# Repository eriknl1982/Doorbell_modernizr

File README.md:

This repository contains sample code and eagle/gerber/STL files for the Doorbell Modernizr I sell on tindie: https://www.tindie.com/products/ErikLemcke/doorbell-modernizr/

The Doorbell Modernizr is a device that can transform your ordinary doorbell (running on 8 - 24v ac) into a "smart" wifi doorbell.
Whenever someone presses your doorbell, the Doorbell Modernizr can send a signal to your home automation system (currently supported: Home assistant, Domoticz and Openhab).

If you want to program the device yourself (for example with the Arduino IDE),provide it with power, plug in a ftdi module and set the dipswitch on the pcb to on.

I use the folowing settings for programming:

- Board: Generic EP8266 module
- Flash mode: QIO
- Flash size: 512K (64K SPIFFS)
- Debugging port: Disabled
- Debug level: None
- IwIP variant: V2 lower memory
- reset method: ck
- crystal frequency: 26Mhz
- Flash frequency: 40Mhz
- CPU frequency: 80Mhz
- Builtin led: 2
- Upload speed: 115200
- Erase flash: Only sketch

If you are going to build it yourself, you will need the folowing parts:

#### To assemble this board, you will need the following parts:
- 1x ESP12f module [(sample)](https://www.aliexpress.com/item/ESP8266-Remote-Serial-WIFI-Transceiver-Wireless-Module-Esp-12-AP-STA-TOP/32646271039.html?spm=2114.search0104.3.8.2d866f9bg356HJ&ws_ab_test=searchweb0_0,searchweb201602_4_10152_10709_10151_10065_10344_10068_5722815_10342_10343_10340_5722915_10341_5722615_10696_10084_10083_10618_10304_10710_10307_10301_5722715_5711215_10059_308_100031_10103_10624_10623_10622_5711315_5722515_10621_10620,searchweb201603_36,ppcSwitch_5&algo_expid=2d4aea06-a96e-40a3-a231-87c2b62a80c4-1&algo_pvid=2d4aea06-a96e-40a3-a231-87c2b62a80c4&transAbTest=ae803_2&priceBeautifyAB=0)
- 4x 10k resitor, smd size 1206 [(sample)](https://www.aliexpress.com/item/Free-Shipping-100PCS-1206-10K-10K-OHM-1-smd-resistor/1090806202.html?spm=2114.search0104.3.1.43a21240XRFdDf&ws_ab_test=searchweb0_0,searchweb201602_4_10152_10709_10151_10065_10344_10068_5722815_10342_10343_10340_5722915_10341_5722615_10696_10084_10083_10618_10304_10710_10307_10301_5722715_5711215_10059_308_100031_10103_10624_10623_10622_5711315_5722515_10621_10620,searchweb201603_36,ppcSwitch_5&algo_expid=709525b8-8593-455c-8efa-07c3f3ce8228-0&algo_pvid=709525b8-8593-455c-8efa-07c3f3ce8228&transAbTest=ae803_2&priceBeautifyAB=0)
- 1x 10k resitor, thru hole [(sample)](https://www.aliexpress.com/store/product/100pcs-set-1-4W-Resistance-1-Metal-Film-Resistor-Pack-Assorted-Kit-1K-2K-4-7K/1504763_32861819464.html?spm=2114.search0104.3.1.4c0d36baXYxkSz&ws_ab_test=searchweb0_0,searchweb201602_4_10152_10151_10065_10344_10068_10342_10343_10340_10341_10696_10084_10083_10618_10304_10307_10820_10821_10301_10843_10059_100031_10103_10624_10623_10622_10621_10620,searchweb201603_51,ppcSwitch_5&algo_expid=e3fd0740-6222-418d-9183-fe36bdfb2f1d-0&algo_pvid=e3fd0740-6222-418d-9183-fe36bdfb2f1d&transAbTest=ae803_2&priceBeautifyAB=0)
- 1x 330r resitor, smd size 1206 [(sample)](https://www.aliexpress.com/item/100Pcs-1206-SMD-resistor-0R-10M-1-2W-0-1-10-100-150-220-330-ohm/32847115923.html?spm=2114.search0104.3.1.4bcc1954MGyEbp&ws_ab_test=searchweb0_0,searchweb201602_4_10152_10709_10151_10065_10344_10068_5722815_10342_10343_10340_5722915_10341_5722615_10696_10084_10083_10618_10304_10710_10307_10301_5722715_5711215_10059_308_100031_10103_10624_10623_10622_5711315_5722515_10621_10620,searchweb201603_36,ppcSwitch_5&algo_expid=03d36d71-9210-4daa-ba6d-0d927a84b877-0&algo_pvid=03d36d71-9210-4daa-ba6d-0d927a84b877&transAbTest=ae803_2&priceBeautifyAB=0)
- 1x 1p dip switch [(sample)](https://www.aliexpress.com/item/10PCS-Lot-DIP-Switch-1P-2-54mm-Toggle-Switch-Red-Snap-Switch/32778200806.html?spm=2114.search0104.3.24.1fe1d1a1sUUCAD&ws_ab_test=searchweb0_0,searchweb201602_4_10152_10709_10151_10065_10344_10068_5722815_10342_10343_10340_5722915_10341_5722615_10696_10084_10083_10618_10304_10710_10307_10301_5722715_5711215_10059_308_100031_10103_10624_10623_10622_5711315_5722515_10621_10620,searchweb201603_36,ppcSwitch_5&algo_expid=cc64cbff-a764-4662-8452-5fbc674b3830-3&algo_pvid=cc64cbff-a764-4662-8452-5fbc674b3830&transAbTest=ae803_2&priceBeautifyAB=0)
- 2x tactile switch [(sample)](https://www.aliexpress.com/item/THGS-25pcs-Round-Pushbutton-4-Pins-SMD-SMT-Momentary-Tactile-Switch/32721411394.html?spm=2114.search0104.3.69.24d25580z5KXIm&ws_ab_test=searchweb0_0,searchweb201602_4_10152_10709_10151_10065_10344_10068_5722815_10342_10343_10340_5722915_10341_5722615_10696_10084_10083_10618_10304_10710_10307_10301_5722715_5711215_10059_308_100031_10103_10624_10623_10622_5711315_5722515_10621_10620,searchweb201603_36,ppcSwitch_5&algo_expid=72ad9c0a-894e-4d0d-a650-c844d18cb295-12&algo_pvid=72ad9c0a-894e-4d0d-a650-c844d18cb295&transAbTest=ae803_2&priceBeautifyAB=0)
- 1x 470uf capacitor [(sample)](https://www.aliexpress.com/item/SMD-electrolytic-capacitor-470UF-6-3V-6-3-7-7MM-VT-type-chip-polarity-temperature-105/32814865187.html?spm=2114.search0104.3.87.3c9272dblaF34k&ws_ab_test=searchweb0_0,searchweb201602_4_10152_10709_10151_10065_10344_10068_5722815_10342_10343_10340_5722915_10341_5722615_10696_10084_10083_10618_10304_10710_10307_10301_5722715_5711215_10059_308_100031_10103_10624_10623_10622_5711315_5722515_10621_10620,searchweb201603_36,ppcSwitch_5&algo_expid=fa08a327-d750-4922-8d0c-8a368b171ecc-13&algo_pvid=fa08a327-d750-4922-8d0c-8a368b171ecc&transAbTest=ae803_2&priceBeautifyAB=0)
- 1x 100nf capacitor, SMD size 1206 [(sample)](https://www.aliexpress.com/item/Free-Shipping-100PCS-1206-104-100NF-0-1UF-1206-SMD-capacitance/1096160798.html?spm=2114.search0104.3.1.71d322c9BiZITD&ws_ab_test=searchweb0_0,searchweb201602_4_10152_10709_10151_10065_10344_10068_5722815_10342_10343_10340_5722915_10341_5722615_10696_10084_10083_10618_10304_10710_10307_10301_5722715_5711215_10059_308_100031_10103_10624_10623_10622_5711315_5722515_10621_10620,searchweb201603_36,ppcSwitch_5&algo_expid=ae9db756-53ad-4fca-853d-d6855f03eda6-0&algo_pvid=ae9db756-53ad-4fca-853d-d6855f03eda6&transAbTest=ae803_2&priceBeautifyAB=0)
- 1x 2pin screw terminal [(sample)](https://www.aliexpress.com/item/20-PCS-KF301-5-0-2P-blue-KF301-3P-Pitch-5-0mm-KF301-2P-Straight-Pin/32833138976.html?spm=2114.search0104.3.17.6b284c7ctDJEA2&ws_ab_test=searchweb0_0,searchweb201602_4_10152_10709_10151_10065_10344_10068_5722815_10342_10343_10340_5722915_10341_5722615_10696_10084_10083_10618_10304_10710_10307_10301_5722715_5711215_10059_308_100031_10103_10624_10623_10622_5711315_5722515_10621_10620,searchweb201603_36,ppcSwitch_5&algo_expid=dd191ab4-0937-468a-a91b-19ac53064bd2-2&algo_pvid=dd191ab4-0937-468a-a91b-19ac53064bd2&transAbTest=ae803_2&priceBeautifyAB=0)
- 1x 6pin female header [(sample)](https://www.aliexpress.com/item/40pcs-2-54MM-6Pin-11MM-Long-Needle-Female-Header-Strip-Stackable-Header-for-arduino-W5100-6p/32668087711.html?spm=2114.search0104.3.83.154721f6xN5o5u&ws_ab_test=searchweb0_0,searchweb201602_4_10152_10709_10151_10065_10344_10068_5722815_10342_10343_10340_5722915_10341_5722615_10696_10084_10083_10618_10304_10710_10307_10301_5722715_5711215_10059_308_100031_10103_10624_10623_10622_5711315_5722515_10621_10620,searchweb201603_36,ppcSwitch_5&algo_expid=c0a98dbf-f354-486c-be51-a9068dfd1d38-12&algo_pvid=c0a98dbf-f354-486c-be51-a9068dfd1d38&transAbTest=ae803_2&priceBeautifyAB=0)
- 1x HT7333 LDO [(sample)](https://www.aliexpress.com/item/10PCS-HT7333-A-SOT-89-HT7333-1-SOT89-HT7333-7333-1-SMD-7333A-1-new-and/32818420909.html?spm=2114.search0104.3.2.4b9c73ea1CR81c&ws_ab_test=searchweb0_0,searchweb201602_4_10152_10709_10151_10065_10344_10068_5722815_10342_10343_10340_5722915_10341_5722615_10696_10084_10083_10618_10304_10710_10307_10301_5722715_5711215_10059_308_100031_10103_10624_10623_10622_5711315_5722515_10621_10620,searchweb201603_36,ppcSwitch_5&algo_expid=5d51c538-7dd5-42bd-8e93-c66127f056bf-0&algo_pvid=5d51c538-7dd5-42bd-8e93-c66127f056bf&transAbTest=ae803_2&priceBeautifyAB=0)
- 1x 1N4148 diode, smd size 1206 [(sample)](https://www.aliexpress.com/item/100pcs-1206-1N4148W-T4-1N4148-SOD-123-Switching-Diode/32354597825.html?spm=2114.search0104.3.1.65002565fkmX0i&ws_ab_test=searchweb0_0,searchweb201602_4_10152_10709_10151_10065_10344_10068_5722815_10342_10343_10340_5722915_10341_5722615_10696_10084_10083_10618_10304_10710_10307_10301_5722715_5711215_10059_308_100031_10103_10624_10623_10622_5711315_5722515_10621_10620,searchweb201603_36,ppcSwitch_5&algo_expid=7cf2de10-d2b9-41eb-a268-300ace100396-0&algo_pvid=7cf2de10-d2b9-41eb-a268-300ace100396&transAbTest=ae803_2&priceBeautifyAB=0)
- 1x PC817 Optocoupler [(sample)](https://www.aliexpress.com/item/100PCS-PC817C-DIP-PC817-C-DIP4-PC817-C-new-and-original-IC-free-shipping/32847601895.html?spm=2114.search0104.3.9.32aa76dfaNDbvv&ws_ab_test=searchweb0_0,searchweb201602_4_10152_10709_10151_10065_10344_10068_5722815_10342_10343_10340_5722915_10341_5722615_10696_10084_10083_10618_10304_10710_10307_10301_5722715_5711215_10059_308_100031_10103_10624_10623_10622_5711315_5722515_10621_10620,searchweb201603_36,ppcSwitch_5&algo_expid=e8d061c3-7004-462e-899c-a522d5885630-1&algo_pvid=e8d061c3-7004-462e-899c-a522d5885630&transAbTest=ae803_2&priceBeautifyAB=0)
- 1x 5.5 x 2.1 mm Female DC Power Jack Plug Socket [sample](https://www.aliexpress.com/item/10Pcs-PCB-Mount-5-5-x-2-1-mm-Female-DC-Power-Jack-Plug-Socket-Connector/32813661863.html?spm=2114.search0104.3.181.7aee2436K2nMqV&ws_ab_test=searchweb0_0,searchweb201602_4_10152_10709_10151_10065_10344_10068_5722815_10342_10343_10340_5722915_10341_5722615_10696_10084_10083_10618_10304_10710_10307_10301_5722715_5711215_10059_308_100031_10103_10624_10623_10622_5711315_5722515_10621_10620,searchweb201603_36,ppcSwitch_5&algo_expid=b89433cb-84ea-4f2c-b110-90657c1acf5a-26&algo_pvid=b89433cb-84ea-4f2c-b110-90657c1acf5a&transAbTest=ae803_2&priceBeautifyAB=0)
- 1x 5v power supply [sample](https://www.aliexpress.com/item/1PCS-High-quality-AC-100V-240V-Converter-Switching-power-adapter-DC-5V-2A-2000MA-Supply-EU/32496043021.html?spm=2114.search0104.3.1.61197a5aNbvepX&ws_ab_test=searchweb0_0,searchweb201602_4_10152_10709_10151_10065_10344_10068_5722815_10342_10343_10340_5722915_10341_5722615_10696_10084_10083_10618_10304_10710_10307_10301_5722715_5711215_10059_308_100031_10103_10624_10623_10622_5711315_5722515_10621_10620,searchweb201603_36,ppcSwitch_5&algo_expid=0f10a11c-3fea-4ce8-9680-a6fa20d2b76d-3&algo_pvid=0f10a11c-3fea-4ce8-9680-a6fa20d2b76d&transAbTest=ae803_2&priceBeautifyAB=0)
- 1x MB6S bridge rectifier [sample](https://www.aliexpress.com/item/Free-shipping-20pcs-600V-0-5A-SOP-4-SMD-rectifier-diode-bridge-mb6s/32336867082.html?spm=2114.search0104.3.1.25d453e0kUU3ZK&ws_ab_test=searchweb0_0,searchweb201602_3_10152_10151_10065_10344_10068_5723115_5722815_10342_10343_10340_5722915_10341_5722615_10696_10084_10083_10618_10304_10307_10820_10301_10821_5722715_10843_10059_100031_10103_10624_10623_10622_5722515_10621_10620,searchweb201603_50,ppcSwitch_5&algo_expid=d8bc8f3c-cd8b-4e61-a706-30cb63aab87a-0&algo_pvid=d8bc8f3c-cd8b-4e61-a706-30cb63aab87a&transAbTest=ae803_2&priceBeautifyAB=0)

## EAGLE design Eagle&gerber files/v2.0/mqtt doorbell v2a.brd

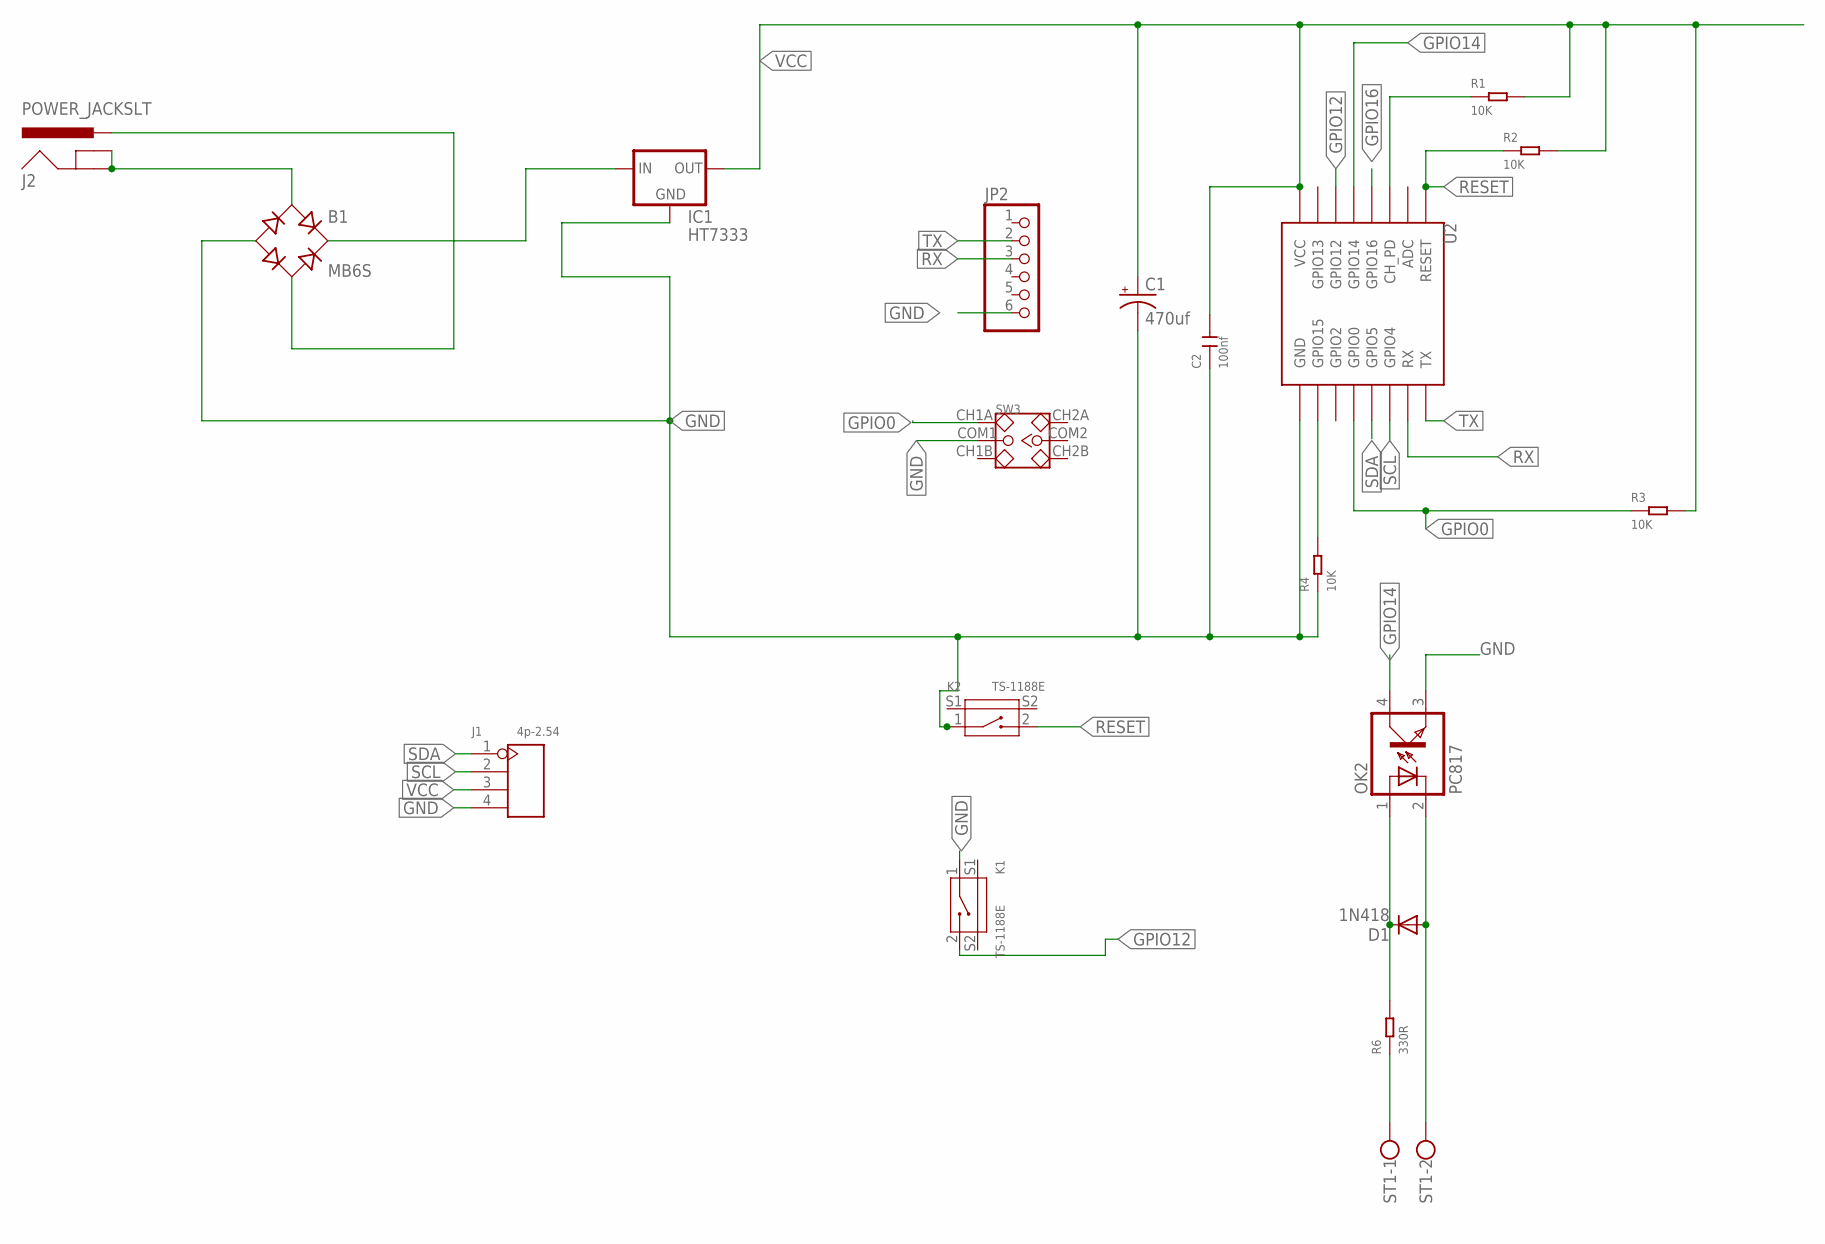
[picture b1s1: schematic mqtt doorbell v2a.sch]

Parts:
B1: MB6S; SOIC-4
C1: 470uf; PANASONIC_D
C2: 100nf; C0603
D1: 1N418; SOD-123_MINI-SMA
IC1: HT7333; SOT-89
J1: 4p-2.54; H4-2.54
J2: POWER_JACKSLT; POWER_JACK_SLOT
JP2: PINHD-1X6; 1X06
K1, K2: TS-1188E; SW4-SMD-7.0X3.5X3.5MM-90D
OK2: PC817; SOP-4-2.54
R1, R2, R3, R4: 10K; R0603
R6: 330R; R0603
ST1: W237-102
SW3: SMD-TOGGLE-SWITCH-2CH(2X3P-7X3.5MM); SW6-2.54-SMD-7.0X3.5X1.5MM
U2: ESP12SMD; ESP12-SMD

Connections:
GND: B1.-, C1.-, C2.1, IC1.2 (GND), J1.4, JP2.6, K1.1, K2.1, OK2.3 (EMIT), R4.1, SW3.COM1, U2.GND
GPIO0: R3.1, SW3.CH1A, U2.GPIO0
GPIO12: K1.2, U2.GPIO12
GPIO14: OK2.4 (COL), U2.GPIO14
GPIO16: U2.GPIO16
L1: B1.+, IC1.3 (IN), IC1.4 (IN)
unnamed: B1.~2 (AC2), J2.PWR
unnamed: D1.C, OK2.1 (A), R6.2
unnamed: D1.A, OK2.2 (C), ST1.2
unnamed: R1.1, U2.CH_PD
unnamed: R6.1, ST1.1
unnamed: R4.2, U2.GPIO15
unnamed: B1.~1 (AC1), J2.GND@1 (GNDBREAK), J2.GND@2 (GND)
RESET: K2.2, R2.1, U2.RESET
RX: JP2.3, U2.RXD0 (RX)
SCL: J1.2, U2.GPIO4
SDA: J1.1, U2.GPIO5
TX: JP2.2, U2.TXD0 (TX)
VCC: C1.+, C2.2, IC1.1 (OUT), J1.3, R1.2, R2.2, R3.2, U2.VCC

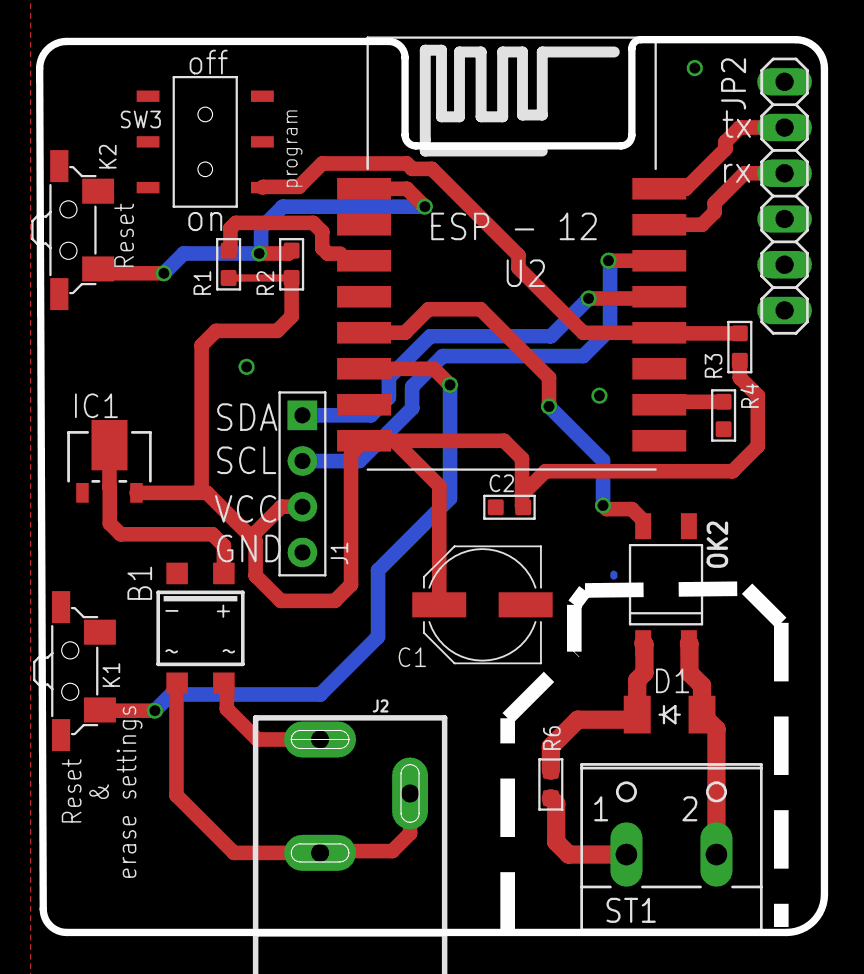
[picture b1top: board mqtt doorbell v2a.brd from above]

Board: 2 copper layers, 43.6 x 49.6 mm, 19 parts (0 on the bottom side), 18 nets.

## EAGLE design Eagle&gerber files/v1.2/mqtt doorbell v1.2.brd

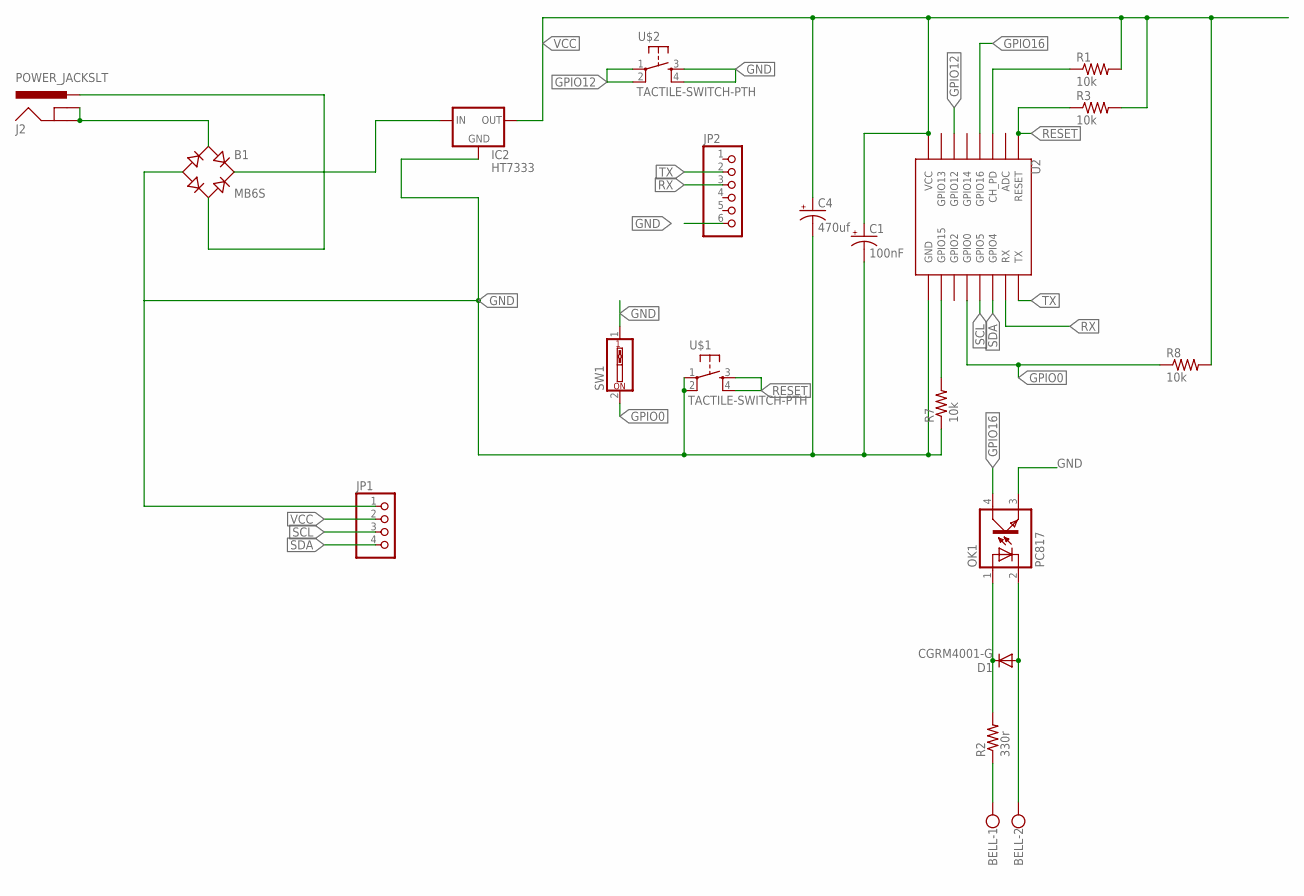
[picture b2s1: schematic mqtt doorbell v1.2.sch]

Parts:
B1: MB6S; SOIC-4
BELL: W237-102
C1: 100nF; EIA3216
C4: 470uf; PANASONIC_D
D1: CGRM4001-G; SOD-123_MINI-SMA
IC2: HT7333; SOT-89
J2: POWER_JACKSLT; POWER_JACK_SLOT
JP1: PINHD-1X4; 1X04
JP2: PINHD-1X6; 1X06
OK1: PC817; DIL04
R1, R3, R7, R8: 10k; 1206
R2: 330r; 1206
SW1: SW_DIP-1; EDG-01
U2: ESP12SMD; ESP12-SMD
U$1, U$2: TACTILE-SWITCH-PTH; TAC-SWITCH-PTH

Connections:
GND: B1.-, C1.C (-), C4.-, IC2.2 (GND), JP1.1, JP2.6, OK1.3 (EMIT), R7.1, SW1.1, U2.GND, U$1.1, U$1.2, U$2.3, U$2.4
GPIO0: R8.1, SW1.2, U2.GPIO0
GPIO12: U2.GPIO12, U$2.1, U$2.2
GPIO16: OK1.4 (COL), U2.GPIO16
unnamed: B1.~2 (AC2), J2.PWR
unnamed: D1.C, OK1.1 (A), R2.2
unnamed: BELL.2, D1.A, OK1.2 (C)
unnamed: R1.1, U2.CH_PD
unnamed: BELL.1, R2.1
unnamed: R7.2, U2.GPIO15
unnamed: B1.~1 (AC1), J2.GND@1 (GNDBREAK), J2.GND@2 (GND)
unnamed: B1.+, IC2.3 (IN), IC2.4 (IN)
RESET: R3.1, U2.RESET, U$1.3, U$1.4
RX: JP2.3, U2.RXD0 (RX)
SCL: JP1.3, U2.GPIO5
SDA: JP1.4, U2.GPIO4
TX: JP2.2, U2.TXD0 (TX)
VCC: C1.A (+), C4.+, IC2.1 (OUT), JP1.2, R1.2, R3.2, R8.2, U2.VCC

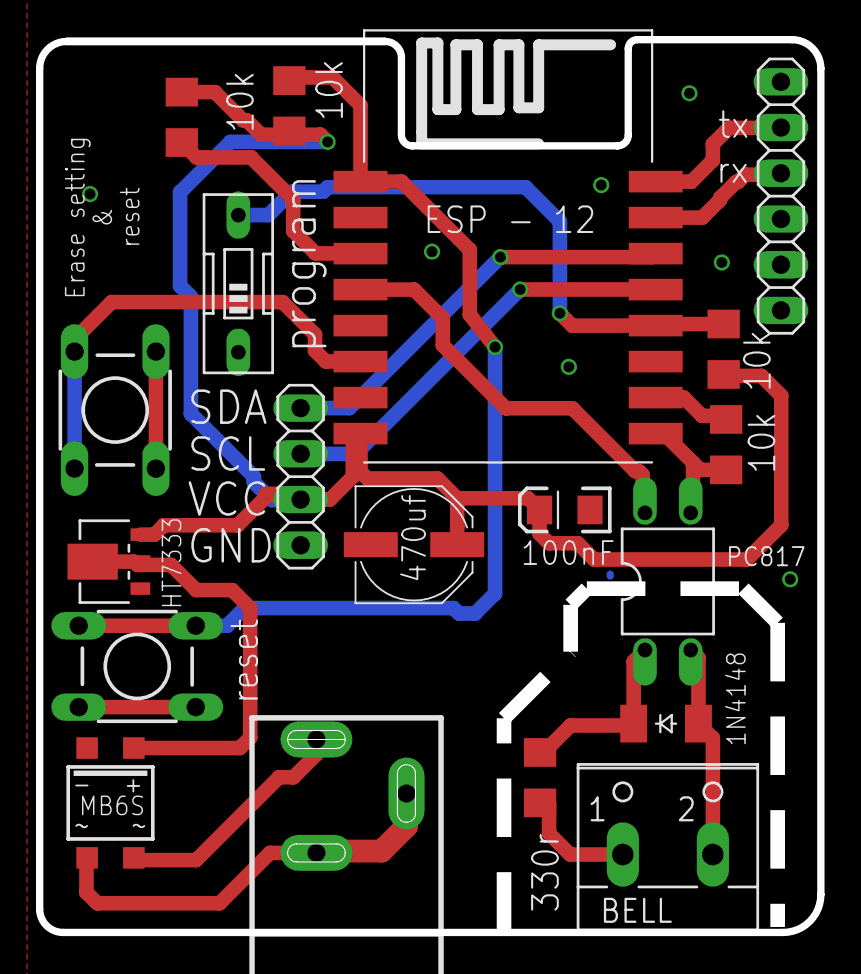
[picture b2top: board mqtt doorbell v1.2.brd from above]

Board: 2 copper layers, 43.4 x 49.6 mm, 19 parts (0 on the bottom side), 18 nets.

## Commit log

2018-05-11 start
2018-05-18 Added schematics
2018-06-18 added wifimanager sample
2018-06-22 much improved wifimanager version
2018-07-08 eagle & gerber files for v1.1
2018-07-20 added 3d print files
2018-08-02 Files for v1.2
2018-08-09 3d print files for v1.2
2018-09-13 sample source for v1.2a
2018-09-13 files for v1.2a
2018-11-05 added manual
2018-11-05 files for v2.0

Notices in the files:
parts and their libraries:
SparkFun-Capacitors: Licensing: Creative Commons ShareAlike 4.0 International - https://creativecommons.org/licenses/by-sa/4.0
